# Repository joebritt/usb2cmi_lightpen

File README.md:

# usb2cmi_lightpen
Use a USB mouse instead of (or in conjunction with) the lightpen on a Fairlight CMI.

# Basic Idea

The interface generates lightpen emulation signals that make the CMI video hardware "think" a lightpen is there. The signals are generated to create a small (smaller than is normal with the real lightpen) cursor on the screen.

Moving the mouse, you will see the on-screen cursor track the mouse movement.

Clicking the left button (or button, if it's a 1-button mouse) is like touching the tip of the real lightpen.

If the mouse has a right button, clicking it will toggle the cursor off and on.

If a real lightpen is fitted to the VDU, it will continue to work in conjunction with the mouse.
Normally, the mouse cursor will be shown on the screen. If you bring the lightpen to the screen,
the lightpen cursor will appear and the mouse cursor will disappear. You can then interact using
the lightpen as normal. When you move the lightpen away from the screen, the mouse cursor will
reappear.

# Version 1
[Version 1 PCB](https://oshpark.com/shared_projects/1uISLCAx)</br>

V1 is the original external box style interface. It is powered by a 5V AC adapter.

Both versions have 2 LEDs. These are used to show the status of the video signal (flashes if no video
detected) and presence of a mouse (off if no mouse detected).

V1 has an RCA jack which provides unbuffered access to the CMI video signal. Since it is
unbuffered, the legacy VDU cannot (normally) be used at the same time as the RCA jack.
(V2 buffers the video signal to allow this use case.)

# Version 2
[Version 2 PCB](https://oshpark.com/shared_projects/5qV4mRA7)</br>

V2 is an updated version that fits completely inside the CMI. It is the same core hardware design.

Differences:
  - No AC power supply needed, it is powered from 5V that is tapped from the CMI front panel board
  - RCA jack provides a buffered CMI video signal, so it and the VDU may be used simultaneously
  - Video RCA jack and USB connector are routed to a panel that mounts to the CMI bottom pan
  - laser-cut "wings" attach to the interface board and let it occupy an unused CMI slot

The CMI Series I and II have a slightly different connection to the front panel board. On those
machines, an adapter board is used to convert to a IIX-style connector that the interface board
can connect to.

## Firmware

Some work will be needed to get the code to build with the latest Microchip MPLAB X tools,
so I recommend installing the v8.63 release of MPLAB (pre-MPLAB X). 

Microchip is good about making legacy tools available, you can find version 8.63 here:

https://www.microchip.com/development-tools/pic-and-dspic-downloads-archive

*You don't have to build the code from source:*

In the "prebuilt_hexfiles" folder are pre-compiled images of the bootloader and lightpen emulation application.

To use these:

- Use the Microchip tools to flash bootloader.hex into the PIC32.
- Put cmimouse.hex on a USB thumbdrive (formatted with a DOS/FAT filesystem).
- Plug the thumbdrive into the interface USB port and power up the board.
- You should see the leds blink back and forth, then the cmimouse.hex file will be copied from the thumbdrive to the PIC32 flash.
- You'll see the LEDs change their flashing pattern when the code is flashed and started.
- Unplug the thumbdrive, plug in a mouse, and you should see the mouse status LED turn ON.
- If you connect the unit to the CMI and power on the CMI, you should see the video status LED stop flashing and go solid ON, and the cursor appear on the CMI video output.

## Hardware

The PCB design tool Eagle was used for all PCBs. 
The Eagle .brd files can be easily uploaded to OSHPark (https://oshpark.com/) for fabrication. Of course, you can use any board house you like to make them.
All boards are 2 layer, 6mil minimum trace/space, and 10mil minimum drill.

The aluminum front panel (for Version 1) and the aluminum rear panel (for Version 2) were designed using Front Panel Designer and fabricated using Front Panel Express (https://www.frontpanelexpress.com/).
Eagle was used as a crude 2D mechanical CAD for the Version 2 rear panel and the Version 2 mounting wings. 
Board files and generated PDFs and XPS files for these are included. The XPS files were used to drive a laser cutter to make prototypes of the rear panel and to make the actual mounting wings.

## Cabling

### Version 1

The 5-pin XLR cable from the CMI to the monitor ("VDU" in Fairlight parlance) connects
to the box. This cable carries a monochrome composite video signal with PAL timing from the CMI
and 2 TTL level signals from the lightpen to the CMI. 

These 3 signals are carried over 3x 75 ohm coax cables bundled together and sheathed similar to
an analog RGB video cable. The pinout for this cable is not straight-through, please see the
details in the monitor_cable folder.

Using two of these 5-pin XLR cables, the box is connected between the CMI and VDU.
Of course, the box can be used without the VDU, in which case only one 5-pin XLR cable is needed.

### Version 2

Version 2 doesn't need the external 5-pin XLR cabling, but does need several smaller internal cables:

- 1x 26-way ribbon cable with a female IDC connector at each end, taps power from CMI front panel
- 1x (CMI IIX) or 2x (CMI I or II) 10-way ribbon cable with a female IDC connector at each end for video & LP signals
- 1x USB Type A to Type B bulkead connector extension, routes USB connection on board to rear panel
- 1x RCA male/male extension, routes video from RCA jack on board to rear panel RCA jack
- 1x RCA female/female bulkhead connector, pass video from internal extension cable to external jack

## Mounting Hardware

### Version 1

The plastic box that was used for Version 1 is off-the-shelf from Radio Shack. It appears that they
still carry this box: https://www.radioshack.com/products/radioshack-project-enclosure-6x3x2?variant=20332261445

The aluminum front panel is designed to replace the blank aluminum panel that comes with the box.

The PCB attaches to the aluminum front panel with the 4 XLR connector screws and floats inside the box.

### Version 2

The 2 laser-cut plastic wings attach to the PCB with 4x M3 screws, nuts, and lockwashers. There are 2 versions
of the wings -- I thought the originals were a little too long, so I made a version 1cm shorter. Both work fine, but the longer ones may cause the internal USB connector to rub against the inside of the front panel door.

For the rear panel, countersunk holes are provided in the aluminum panel to accept the screws originally used to hold the Fairlight factory-provided blank cover panel. Remove the blank panel, use the screws and nuts to affix the new aluminum video/USB jack panel.

The bulkhead female/female RCA connector has 1 large nut which should be on the inside face of the panel.
The bulkhead USB connector has 2 M3 screws that hold it in place.

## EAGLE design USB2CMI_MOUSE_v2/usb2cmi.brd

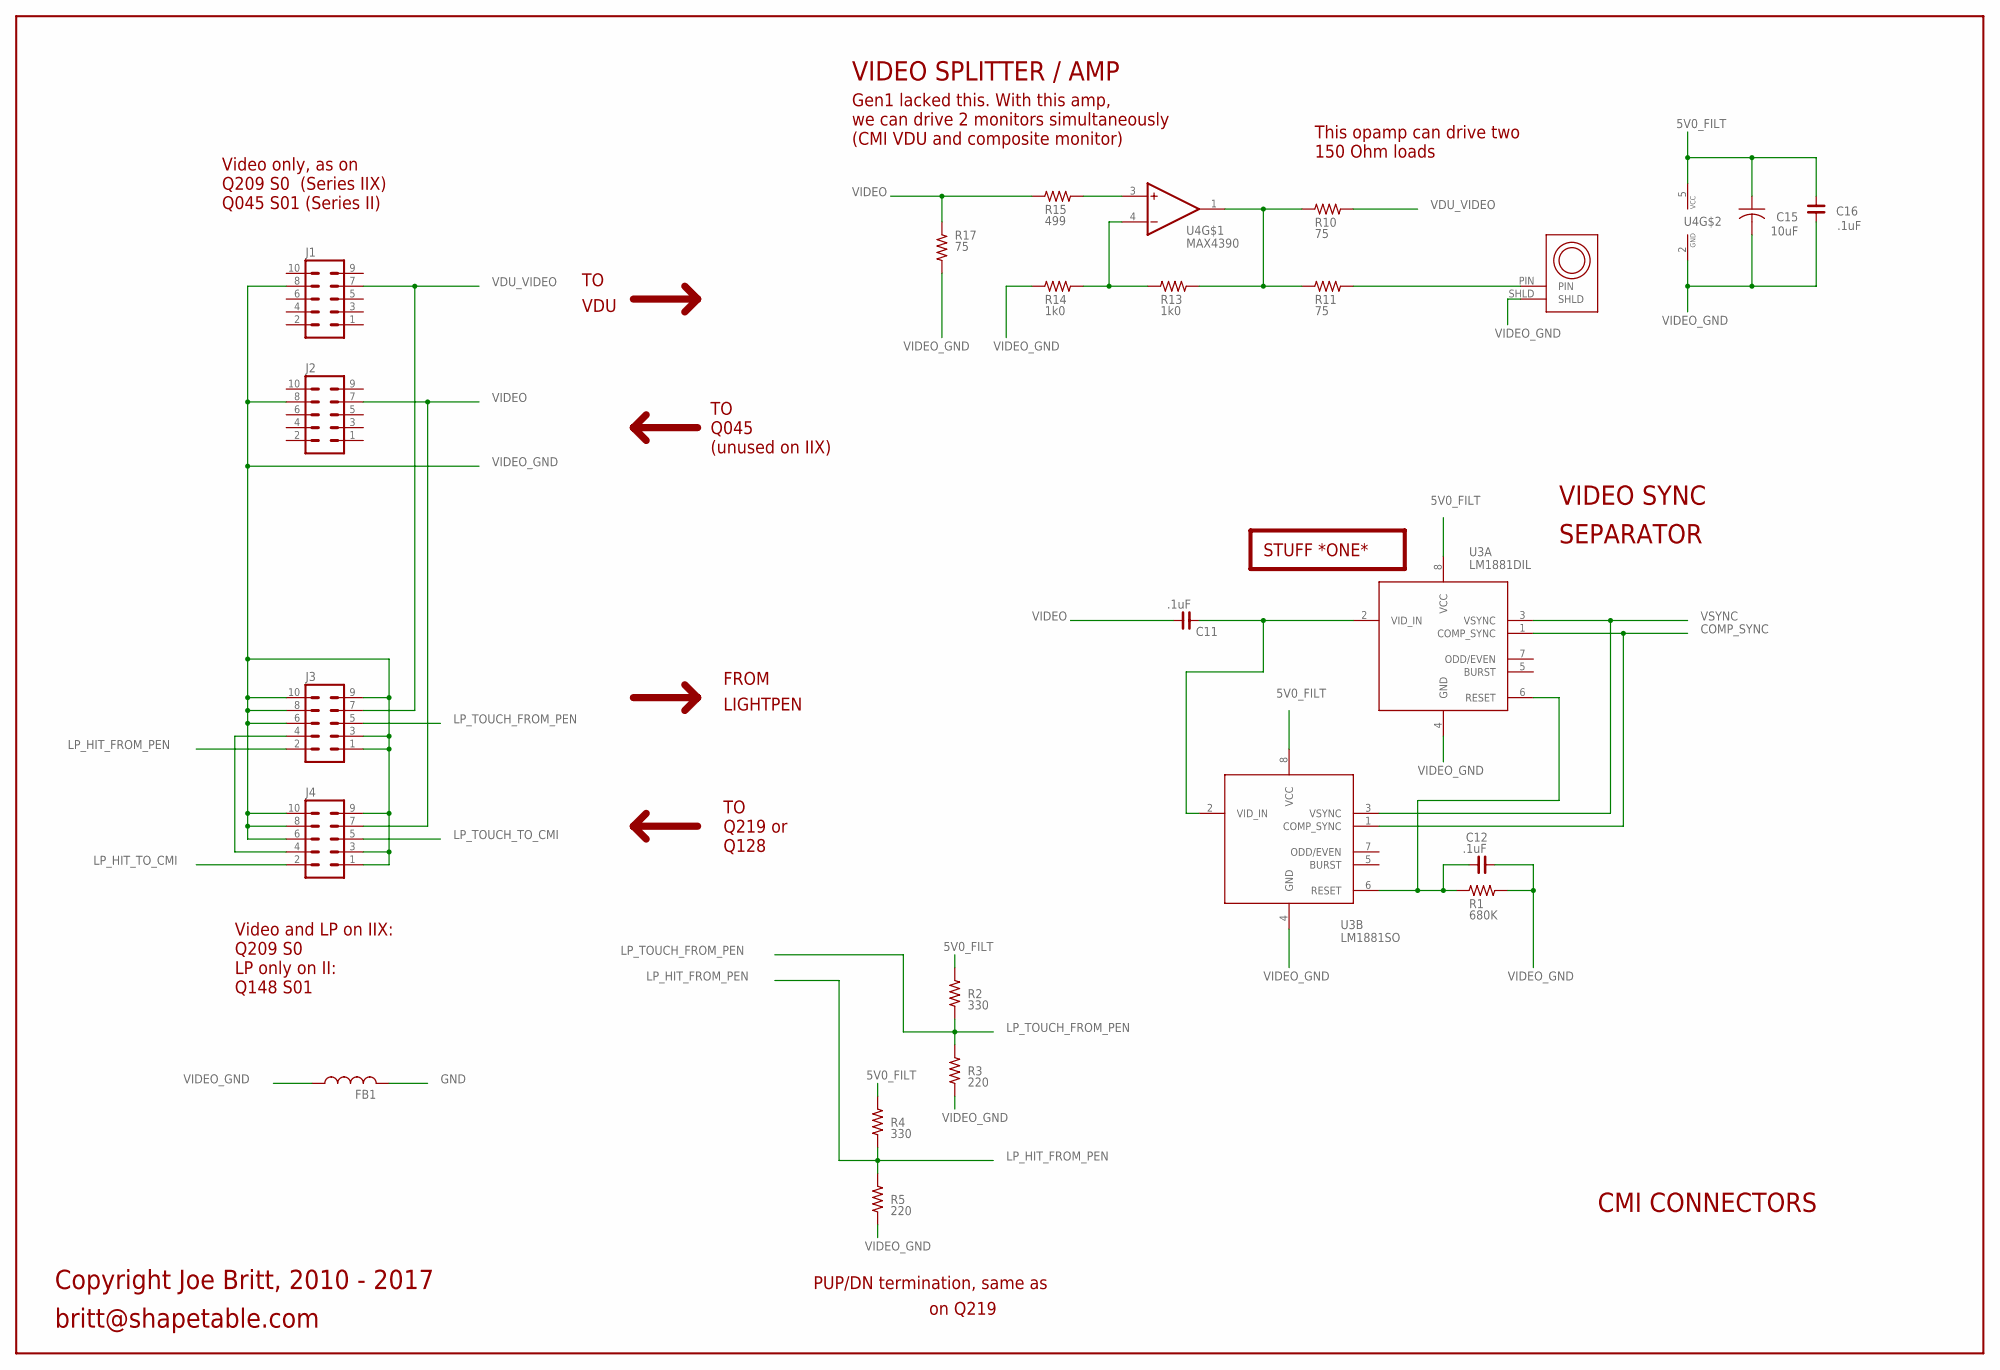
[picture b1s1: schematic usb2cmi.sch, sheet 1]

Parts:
C11, C12, C16: .1uF; C0603
C15: 10uF; C0805
FB1: L-US0207/15; 0207/15
J1, J3: 10H
J2, J4: ML10
J8: CUI RCJ-044; RCA-SHIELDED
R1: 680K; R0603
R2, R4: 330; R0603
R3, R5: 220; R0603
R10, R11, R17: 75; R0603
R13, R14: 1k0; R0603
R15: 499; R0603
U3A: LM1881DIL; DIL08
U3B: LM1881SO; SO08
U4: MAX4390; SOT23-5L

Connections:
5V0_FILT: C15.1, C16.2, R2.2, R4.2, U3A.8 (VCC), U3B.8 (VCC), U4.5 (VCC); also elsewhere on the board
COMP_SYNC: U3A.1 (COMP_SYNC), U3B.1 (COMP_SYNC); also elsewhere on the board
GND: FB1.2; also elsewhere on the board
LP_HIT_FROM_PEN: J3.2, R4.1, R5.2; also elsewhere on the board
LP_HIT_TO_CMI: J4.2; also elsewhere on the board
LP_TOUCH_FROM_PEN: J3.5, R2.1, R3.2; also elsewhere on the board
LP_TOUCH_TO_CMI: J4.5; also elsewhere on the board
unnamed: J3.4, J4.4
unnamed: C11.2, U3A.2 (VID_IN), U3B.2 (VID_IN)
unnamed: C12.1, R1.2, U3A.6 (RESET), U3B.6 (RESET)
unnamed: R10.2, R11.2, R13.1, U4.1 (OUT)
unnamed: J8.PIN, R11.1
unnamed: R13.2, R14.1, U4.4 (-IN)
unnamed: R15.1, U4.3 (+IN)
VDU_VIDEO: J1.7, J3.7, R10.1
VIDEO: C11.1, J2.7, J4.7, R15.2, R17.1
VIDEO_GND: C12.2, C15.2, C16.1, FB1.1, J1.8, J2.8, J3.1, J3.3, J3.6, J3.8, J3.9, J3.10, J4.1, J4.3, J4.6, J4.8, J4.9, J4.10, J8.SHLD, R1.1, R3.1, R5.1, R14.2, R17.2, U3A.4 (GND), U3B.4 (GND), U4.2 (GND); also elsewhere on the board
VSYNC: U3A.3 (VSYNC), U3B.3 (VSYNC); also elsewhere on the board

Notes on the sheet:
VDU
Q045 (unused on IIX)
STUFF *ONE*
VIDEO SYNC
SEPARATOR
CMI CONNECTORS
PUP/DN termination, same as
on Q219
Copyright Joe Britt, 2010 - 2017
britt@shapetable.com
Video only, as on Q209 S0 (Series IIX) Q045 S01 (Series II)
Video and LP on IIX: Q209 S0 LP only on II: Q148 S01
FROM
LIGHTPEN
Q219 or Q128
VIDEO SPLITTER / AMP
Gen1 lacked this. With this amp, we can drive 2 monitors simultaneously (CMI VDU and composite monitor)
This opamp can drive two 150 Ohm loads

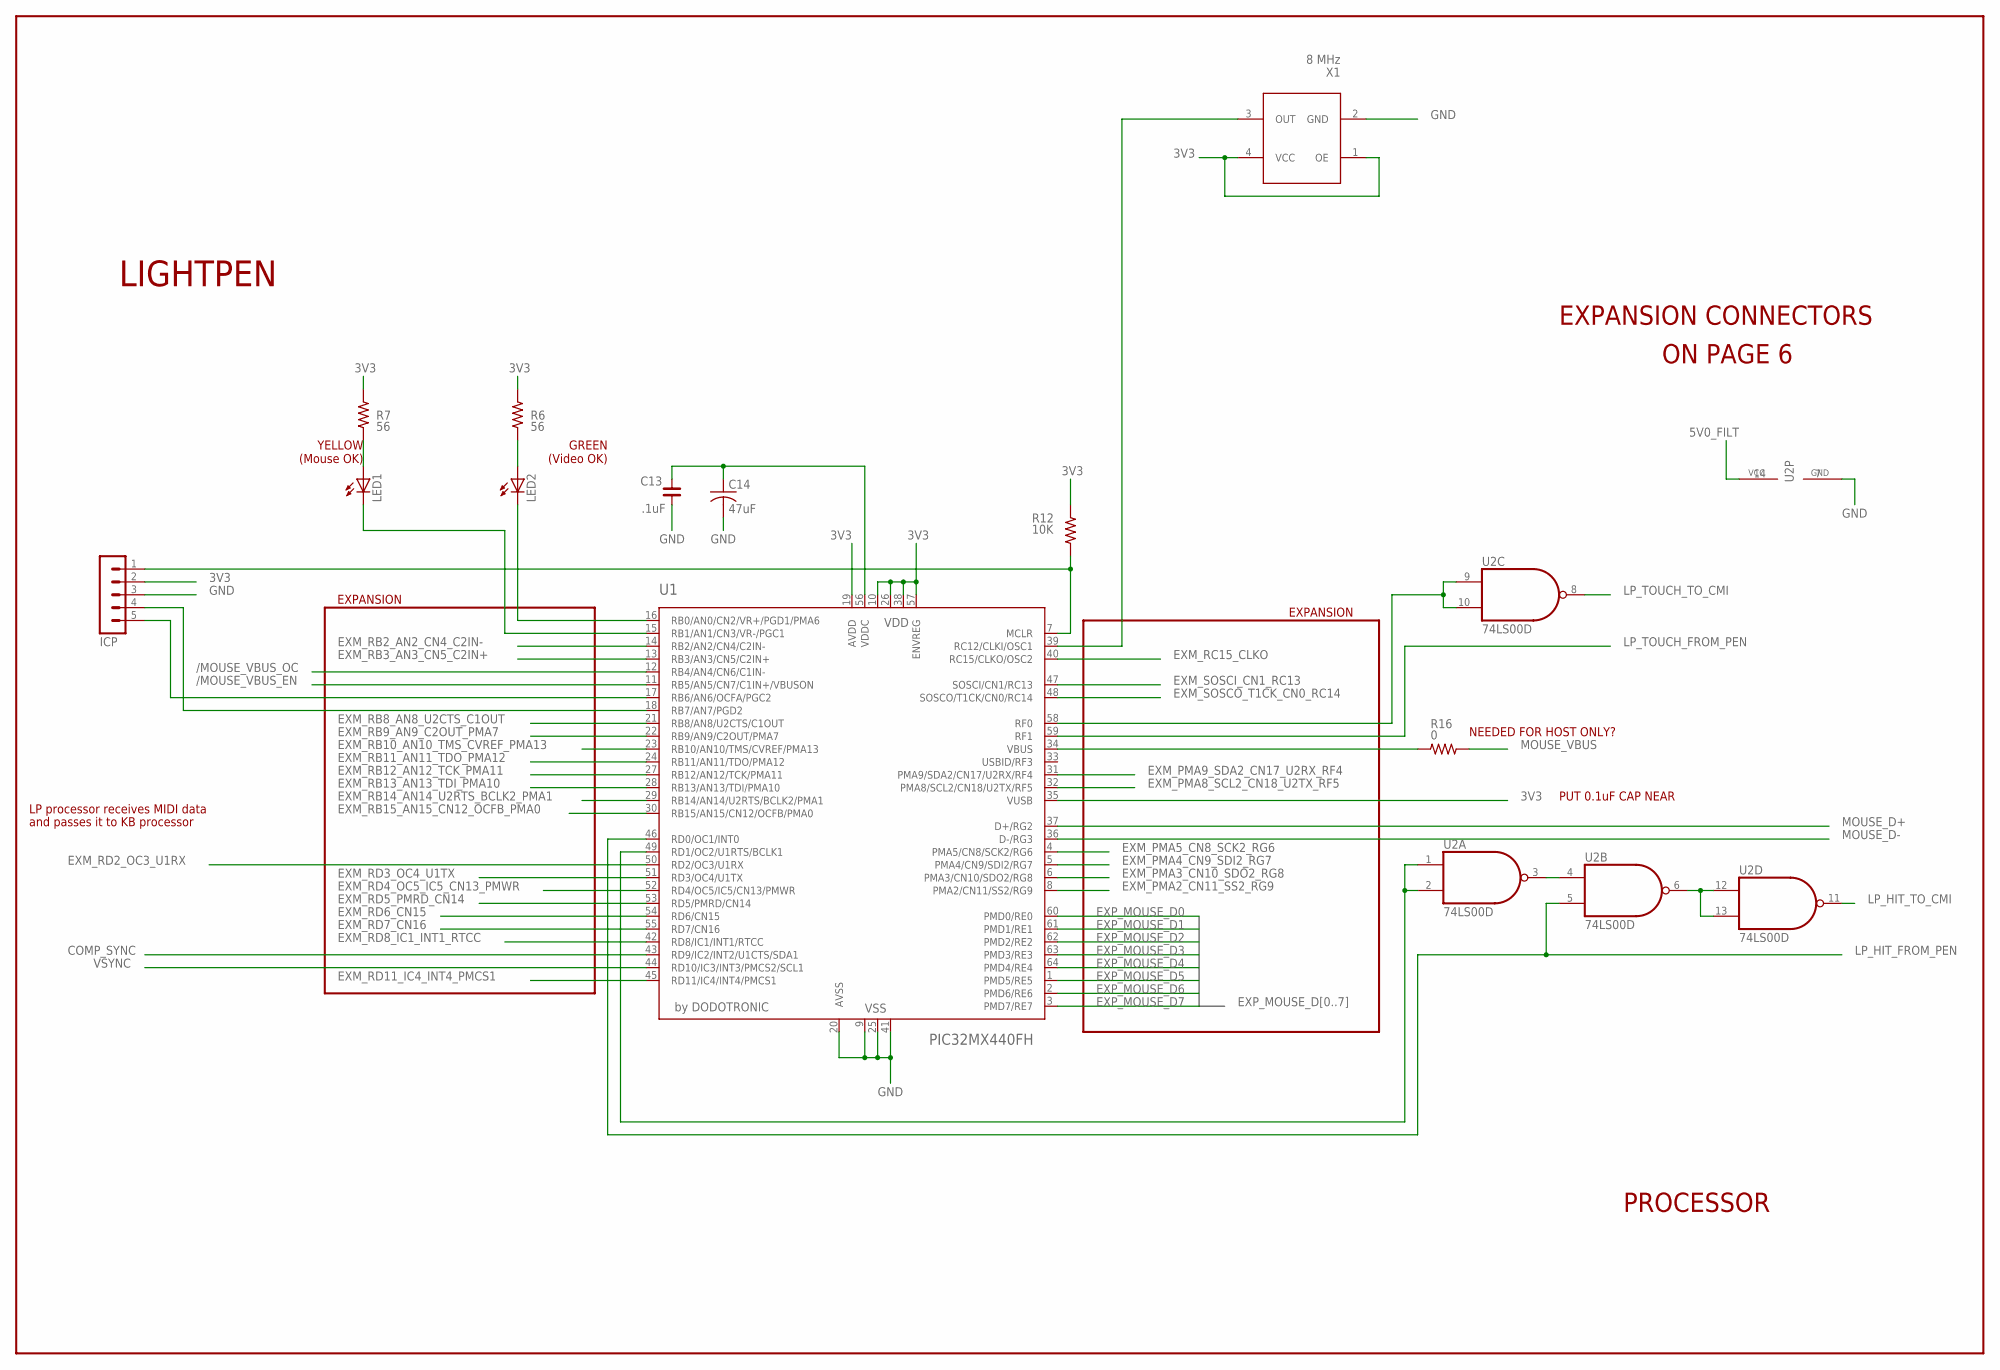
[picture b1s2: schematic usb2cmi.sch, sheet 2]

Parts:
C13: .1uF; C0603
C14: 47uF; C0805
ICP: MA05-1
LED1, LED2: LEDCHIPLED_0805; CHIPLED_0805
R6, R7: 56; R0603
R12: 10K; R0603
R16: 0; R0603
U1: PIC32MX440FH; TQFP64-10X10
U2: 74LS00D; SO14
X1: 8 MHz; CTS-OSC

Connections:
3V3: ICP.2, R6.2, R7.2, R12.2, U1.10 (VDD), U1.19 (AVDD), U1.26 (VDD), U1.35 (VUSB), U1.38 (VDD), U1.57 (ENVREG), X1.1 (OE), X1.4 (VCC); also elsewhere on the board
5V0_FILT: U2.14 (VCC); also elsewhere on the board
/MOUSE_VBUS_EN: U1.11 (RB5/AN5/CN7/C1IN+/VBUSON); also elsewhere on the board
/MOUSE_VBUS_OC: U1.12 (RB4/AN4/CN6/C1IN-); also elsewhere on the board
COMP_SYNC: U1.43 (RD9/IC2/INT2/U1CTS/SDA1); also elsewhere on the board
EXM_PMA2_CN11_SS2_RG9: U1.8 (PMA2/CN11/SS2/RG9)
EXM_PMA3_CN10_SDO2_RG8: U1.6 (PMA3/CN10/SDO2/RG8)
EXM_PMA4_CN9_SDI2_RG7: U1.5 (PMA4/CN9/SDI2/RG7)
EXM_PMA5_CN8_SCK2_RG6: U1.4 (PMA5/CN8/SCK2/RG6)
EXM_PMA8_SCL2_CN18_U2TX_RF5: U1.32 (PMA8/SCL2/CN18/U2TX/RF5); also elsewhere on the board
EXM_PMA9_SDA2_CN17_U2RX_RF4: U1.31 (PMA9/SDA2/CN17/U2RX/RF4); also elsewhere on the board
EXM_RB0_AN0_CN2_PMA6: LED2.C, U1.16 (RB0/AN0/CN2/VR+/PGD1/PMA6)
EXM_RB2_AN2_CN4_C2IN-: U1.14 (RB2/AN2/CN4/C2IN-)
EXM_RB3_AN3_CN5_C2IN+: U1.13 (RB3/AN3/CN5/C2IN+)
EXM_RB8_AN8_U2CTS_C1OUT: U1.21 (RB8/AN8/U2CTS/C1OUT)
EXM_RB9_AN9_C2OUT_PMA7: U1.22 (RB9/AN9/C2OUT/PMA7)
EXM_RB10_AN10_TMS_CVREF_PMA13: U1.23 (RB10/AN10/TMS/CVREF/PMA13)
EXM_RB11_AN11_TDO_PMA12: U1.24 (RB11/AN11/TDO/PMA12)
EXM_RB12_AN12_TCK_PMA11: U1.27 (RB12/AN12/TCK/PMA11)
EXM_RB13_AN13_TDI_PMA10: U1.28 (RB13/AN13/TDI/PMA10)
EXM_RB14_AN14_U2RTS_BCLK2_PMA1: U1.29 (RB14/AN14/U2RTS/BCLK2/PMA1)
EXM_RB15_AN15_CN12_OCFB_PMA0: U1.30 (RB15/AN15/CN12/OCFB/PMA0)
EXM_RC15_CLKO: U1.40 (RC15/CLKO/OSC2)
EXM_RD2_OC3_U1RX: U1.50 (RD2/OC3/U1RX); also elsewhere on the board
EXM_RD3_OC4_U1TX: U1.51 (RD3/OC4/U1TX); also elsewhere on the board
EXM_RD4_OC5_IC5_CN13_PMWR: U1.52 (RD4/OC5/IC5/CN13/PMWR)
EXM_RD5_PMRD_CN14: U1.53 (RD5/PMRD/CN14)
EXM_RD6_CN15: U1.54 (RD6/CN15)
EXM_RD7_CN16: U1.55 (RD7/CN16)
EXM_RD8_IC1_INT1_RTCC: U1.42 (RD8/IC1/INT1/RTCC)
EXM_RD11_IC4_INT4_PMCS1: U1.45 (RD11/IC4/INT4/PMCS1)
EXM_SOSCI_CN1_RC13: U1.47 (SOSCI/CN1/RC13)
EXM_SOSCO_T1CK_CN0_RC14: U1.48 (SOSCO/T1CK/CN0/RC14)
EXP_MOUSE_D0: U1.60 (PMD0/RE0)
EXP_MOUSE_D1: U1.61 (PMD1/RE1)
EXP_MOUSE_D2: U1.62 (PMD2/RE2)
EXP_MOUSE_D3: U1.63 (PMD3/RE3)
EXP_MOUSE_D4: U1.64 (PMD4/RE4)
EXP_MOUSE_D5: U1.1 (PMD5/RE5)
EXP_MOUSE_D6: U1.2 (PMD6/RE6)
EXP_MOUSE_D7: U1.3 (PMD7/RE7)
GND: C13.2, C14.2, ICP.3, U1.9 (VSS), U1.20 (AVSS), U1.25 (VSS), U1.41 (VSS), U2.7 (GND), X1.2 (GND); also elsewhere on the board
LP_HIT_FROM_PEN: U1.46 (RD0/OC1/INT0), U2.5 (I1); also elsewhere on the board
LP_HIT_TO_CMI: U2.11 (O); also elsewhere on the board
LP_TOUCH_FROM_PEN: U1.59 (RF1); also elsewhere on the board
LP_TOUCH_TO_CMI: U2.8 (O); also elsewhere on the board
MOUSE_D+: U1.37 (D+/RG2); also elsewhere on the board
MOUSE_D-: U1.36 (D-/RG3); also elsewhere on the board
MOUSE_VBUS: R16.1; also elsewhere on the board
unnamed: C13.1, C14.1, U1.56 (VDDC)
unnamed: LED2.A, R6.1
unnamed: LED1.C, U1.15 (RB1/AN1/CN3/VR-/PGC1)
unnamed: U1.39 (RC12/CLKI/OSC1), X1.3 (OUT)
unnamed: U1.58 (RF0), U2.9 (I0), U2.10 (I1)
unnamed: U2.6 (O), U2.12 (I0), U2.13 (I1)
unnamed: U2.3 (O), U2.4 (I0)
unnamed: U1.49 (RD1/OC2/U1RTS/BCLK1), U2.1 (I0), U2.2 (I1)
unnamed: LED1.A, R7.1
unnamed: R16.2, U1.34 (VBUS)
PGC: ICP.5, U1.17 (RB6/AN6/OCFA/PGC2)
PGD: ICP.4, U1.18 (RB7/AN7/PGD2)
U2_MCLR: ICP.1, R12.1, U1.7 (MCLR)
VSYNC: U1.44 (RD10/IC3/INT3/PMCS2/SCL1); also elsewhere on the board

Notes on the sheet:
LIGHTPEN
YELLOW (Mouse OK)
NEEDED FOR HOST ONLY?
PUT 0.1uF CAP NEAR
EXPANSION CONNECTORS
ON PAGE 6
PROCESSOR
EXPANSION
LP processor receives MIDI data
and passes it to KB processor
GREEN (Video OK)

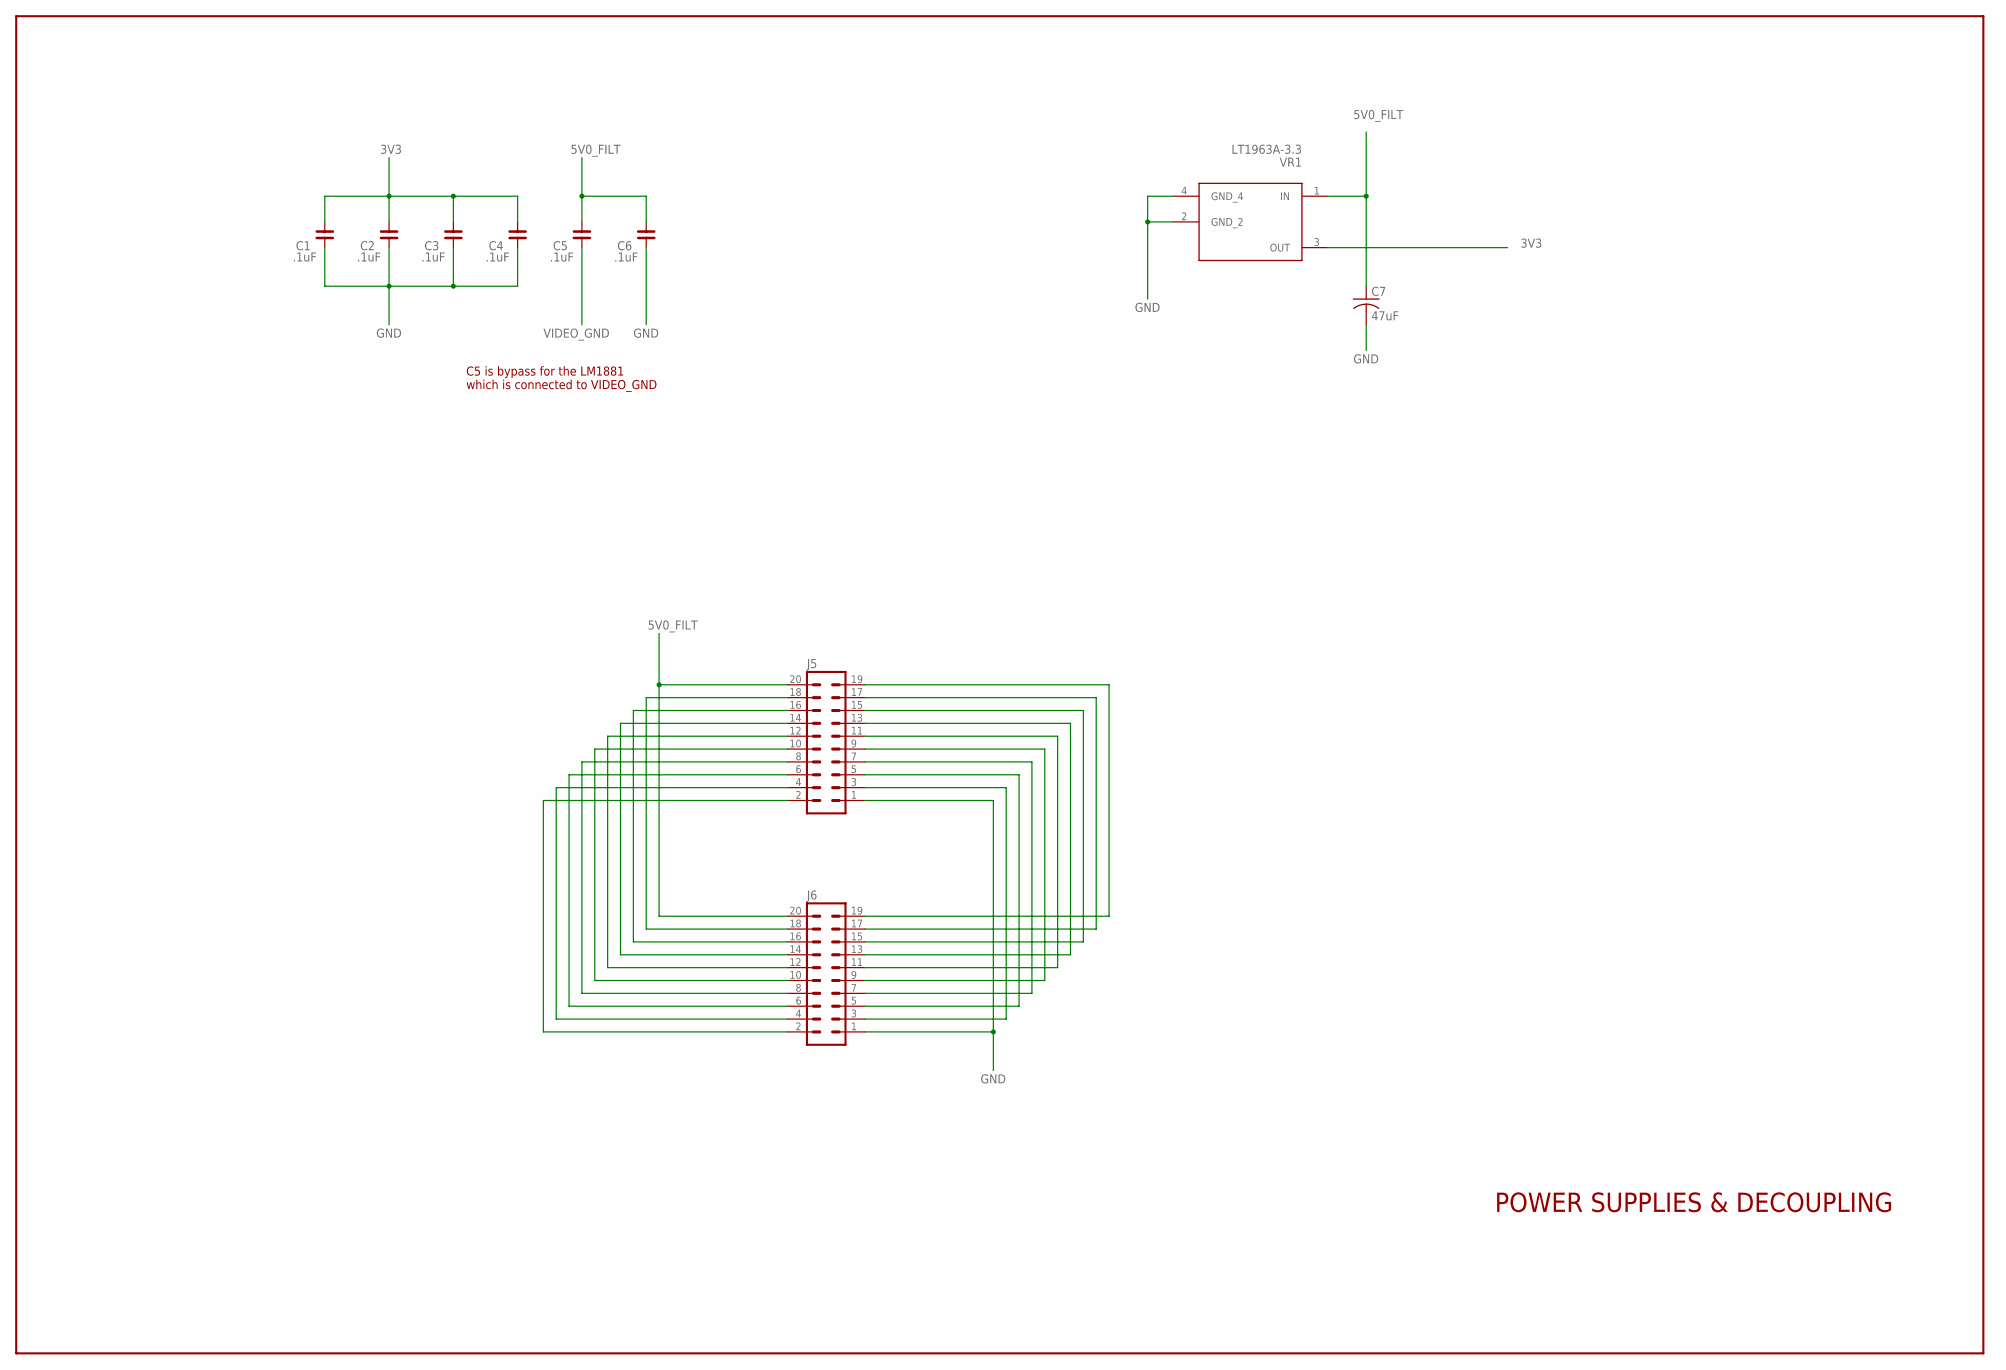
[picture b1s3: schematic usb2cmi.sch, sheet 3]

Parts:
C1, C2, C3, C4, C5, C6: .1uF; C0603
C7: 47uF; C0805
J5: 20H
J6: ML20
VR1: LT1963A-3.3; SOT-223

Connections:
3V3: C1.1, C2.1, C3.1, C4.1, VR1.3 (OUT); also elsewhere on the board
5V0_FILT: C5.1, C6.1, C7.1, J5.20, J6.20, VR1.1 (IN); also elsewhere on the board
GND: C1.2, C2.2, C3.2, C4.2, C6.2, C7.2, J5.1, J6.1, VR1.2 (GND_2), VR1.4 (GND_4); also elsewhere on the board
unnamed: J5.18, J6.18
unnamed: J5.16, J6.16
unnamed: J5.14, J6.14
unnamed: J5.12, J6.12
unnamed: J5.10, J6.10
unnamed: J5.8, J6.8
unnamed: J5.6, J6.6
unnamed: J5.4, J6.4
unnamed: J5.2, J6.2
unnamed: J5.3, J6.3
unnamed: J5.5, J6.5
unnamed: J5.7, J6.7
unnamed: J5.9, J6.9
unnamed: J5.11, J6.11
unnamed: J5.13, J6.13
unnamed: J5.15, J6.15
unnamed: J5.17, J6.17
unnamed: J5.19, J6.19
VIDEO_GND: C5.2; also elsewhere on the board

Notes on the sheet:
POWER SUPPLIES & DECOUPLING
C5 is bypass for the LM1881 which is connected to VIDEO_GND

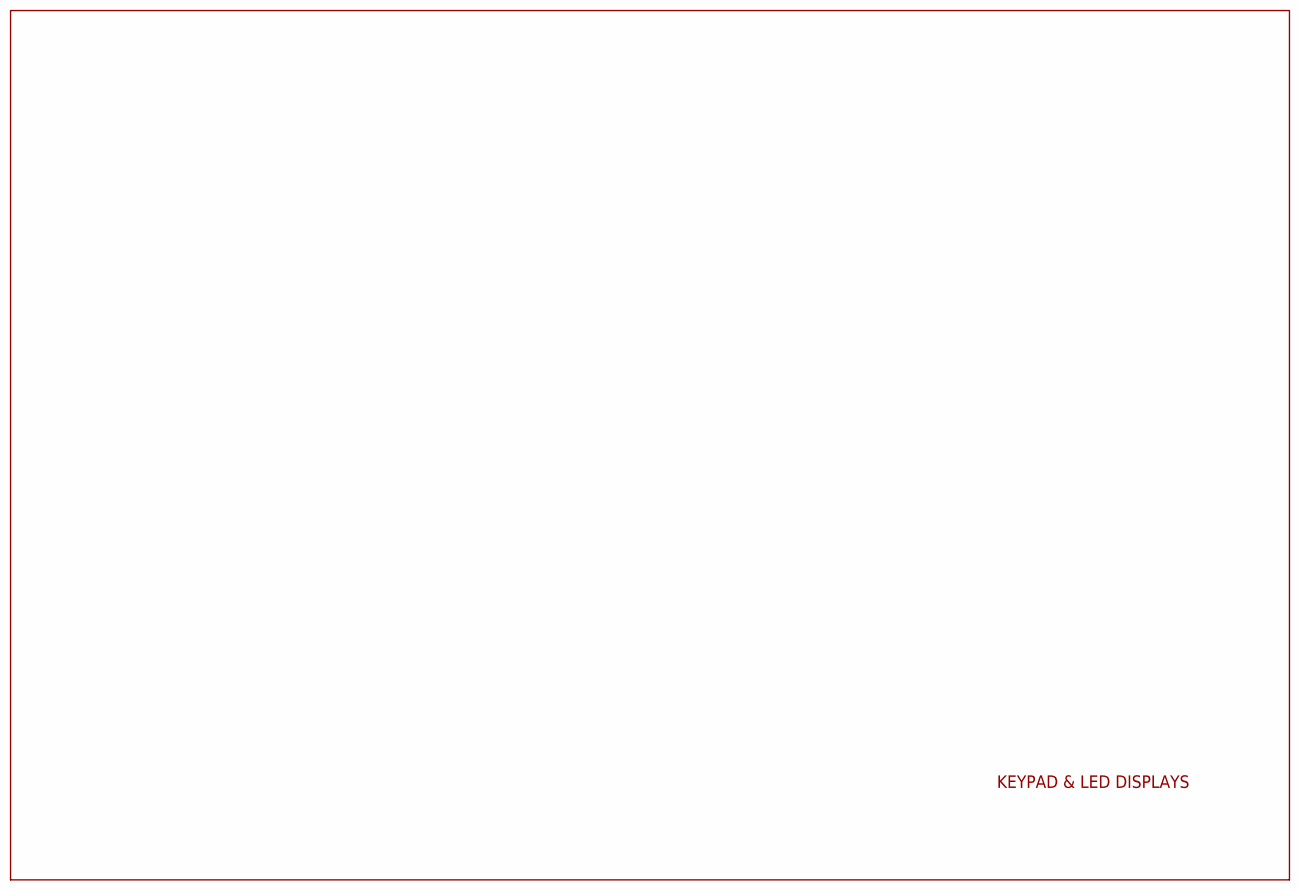
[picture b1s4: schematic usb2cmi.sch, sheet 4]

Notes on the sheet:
KEYPAD & LED DISPLAYS

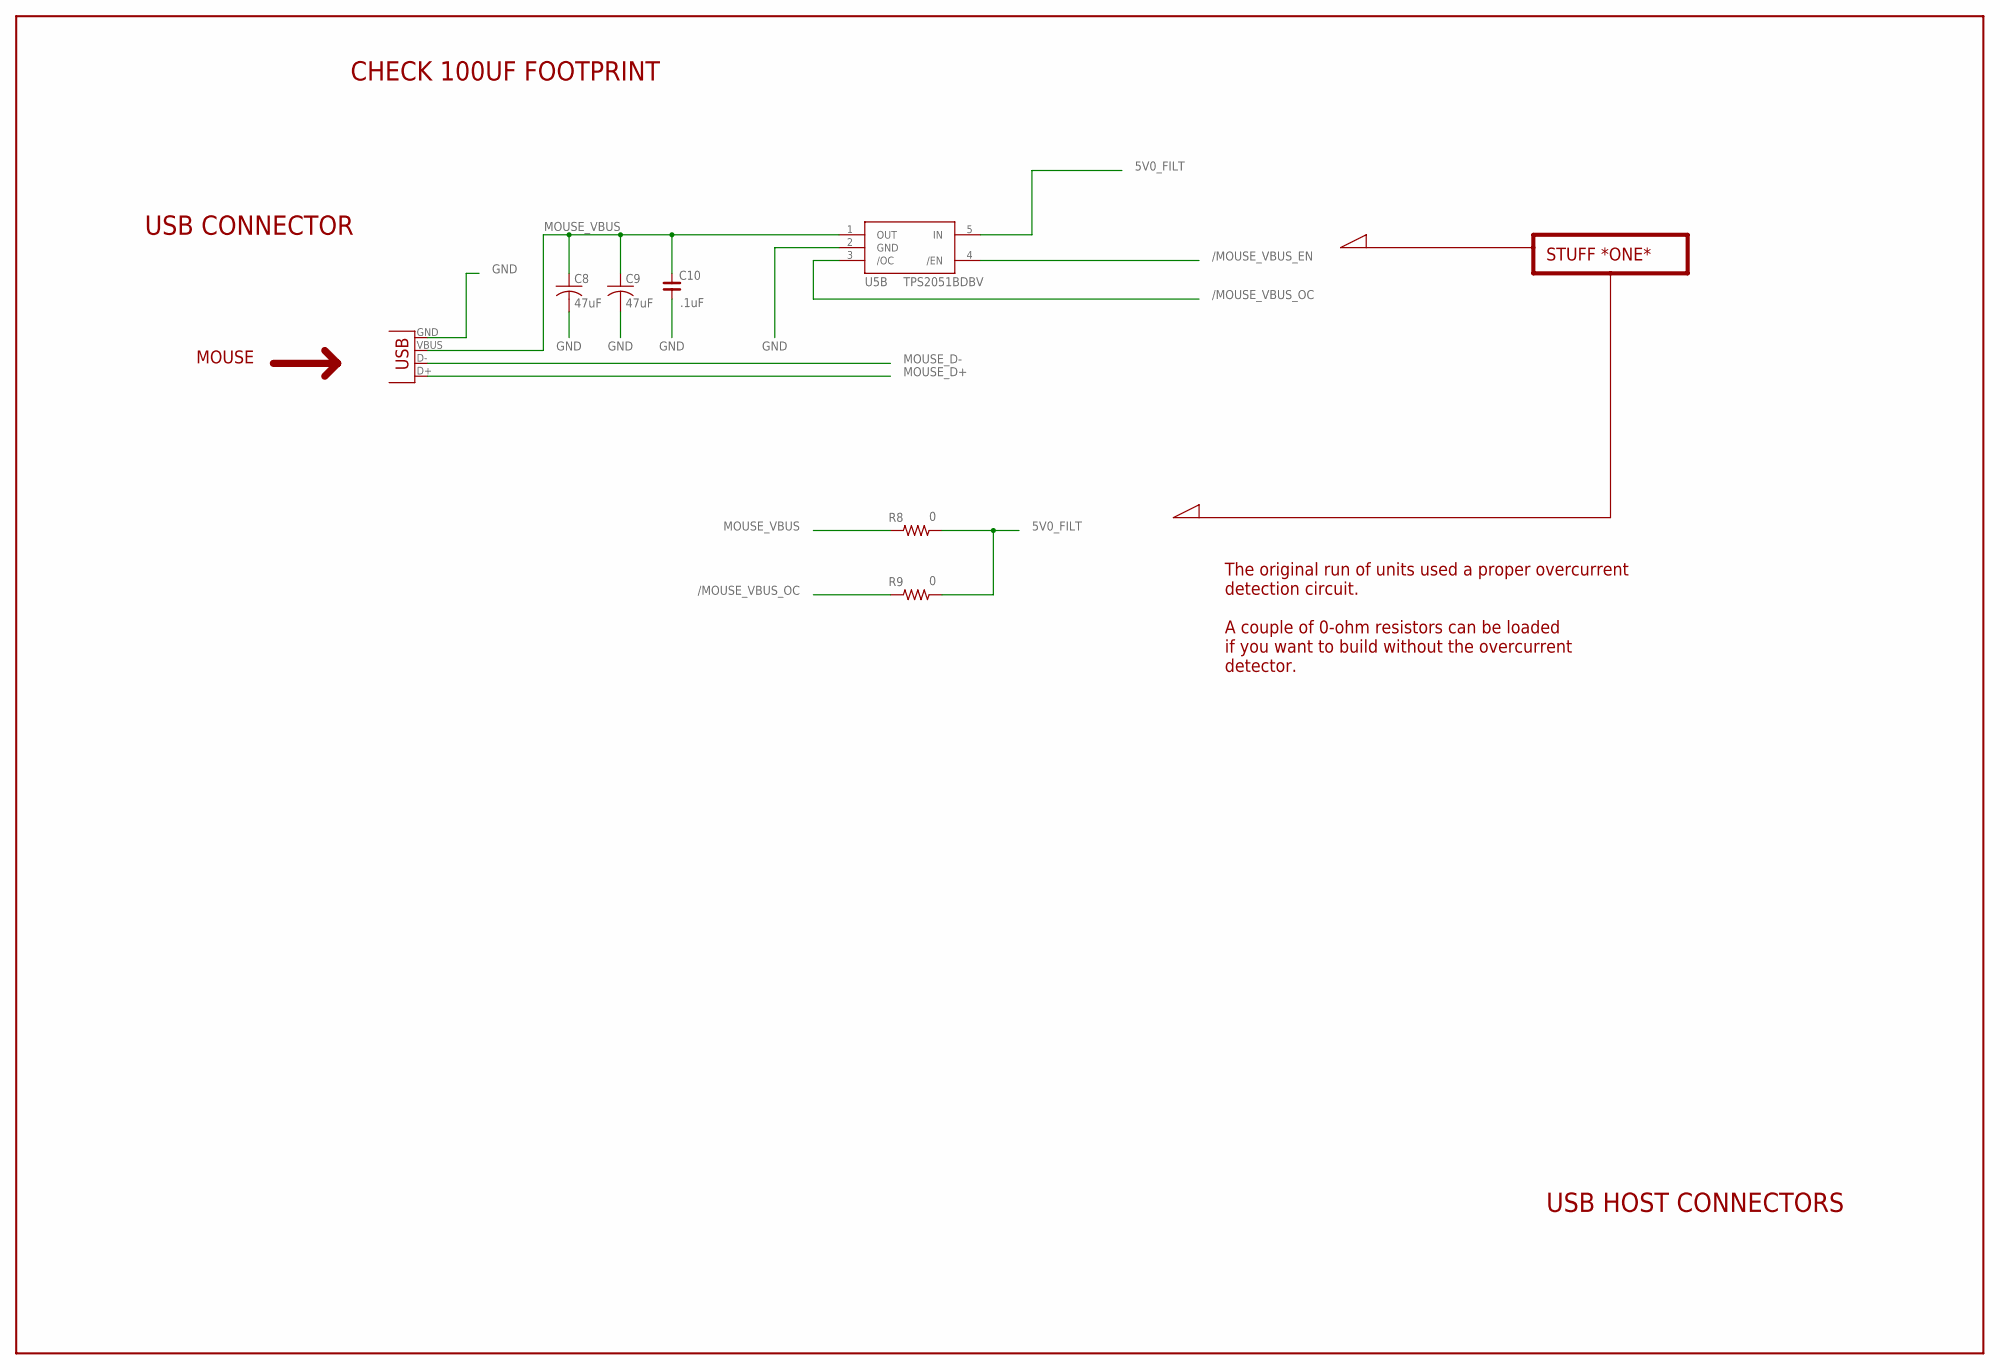
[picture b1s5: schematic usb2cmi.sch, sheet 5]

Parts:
C8, C9: 47uF; C0805
C10: .1uF; C0603
J7: USB-A-H
R8, R9: 0; R0603
U5B: TPS2051BDBV; DBV-5

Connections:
5V0_FILT: R8.1, R9.1, U5B.5 (IN); also elsewhere on the board
/MOUSE_VBUS_EN: U5B.4 (/EN); also elsewhere on the board
/MOUSE_VBUS_OC: R9.2, U5B.3 (/OC); also elsewhere on the board
GND: C8.2, C9.2, C10.2, J7.GND, U5B.2 (GND); also elsewhere on the board
MOUSE_D+: J7.D+; also elsewhere on the board
MOUSE_D-: J7.D-; also elsewhere on the board
MOUSE_VBUS: C8.1, C9.1, C10.1, J7.VBUS, R8.2, U5B.1 (OUT); also elsewhere on the board

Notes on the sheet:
MOUSE
USB CONNECTOR
STUFF *ONE*
CHECK 100UF FOOTPRINT
USB HOST CONNECTORS
The original run of units used a proper overcurrent detection circuit. A couple of 0-ohm resistors can be loaded if you want to build without the overcurrent detector.

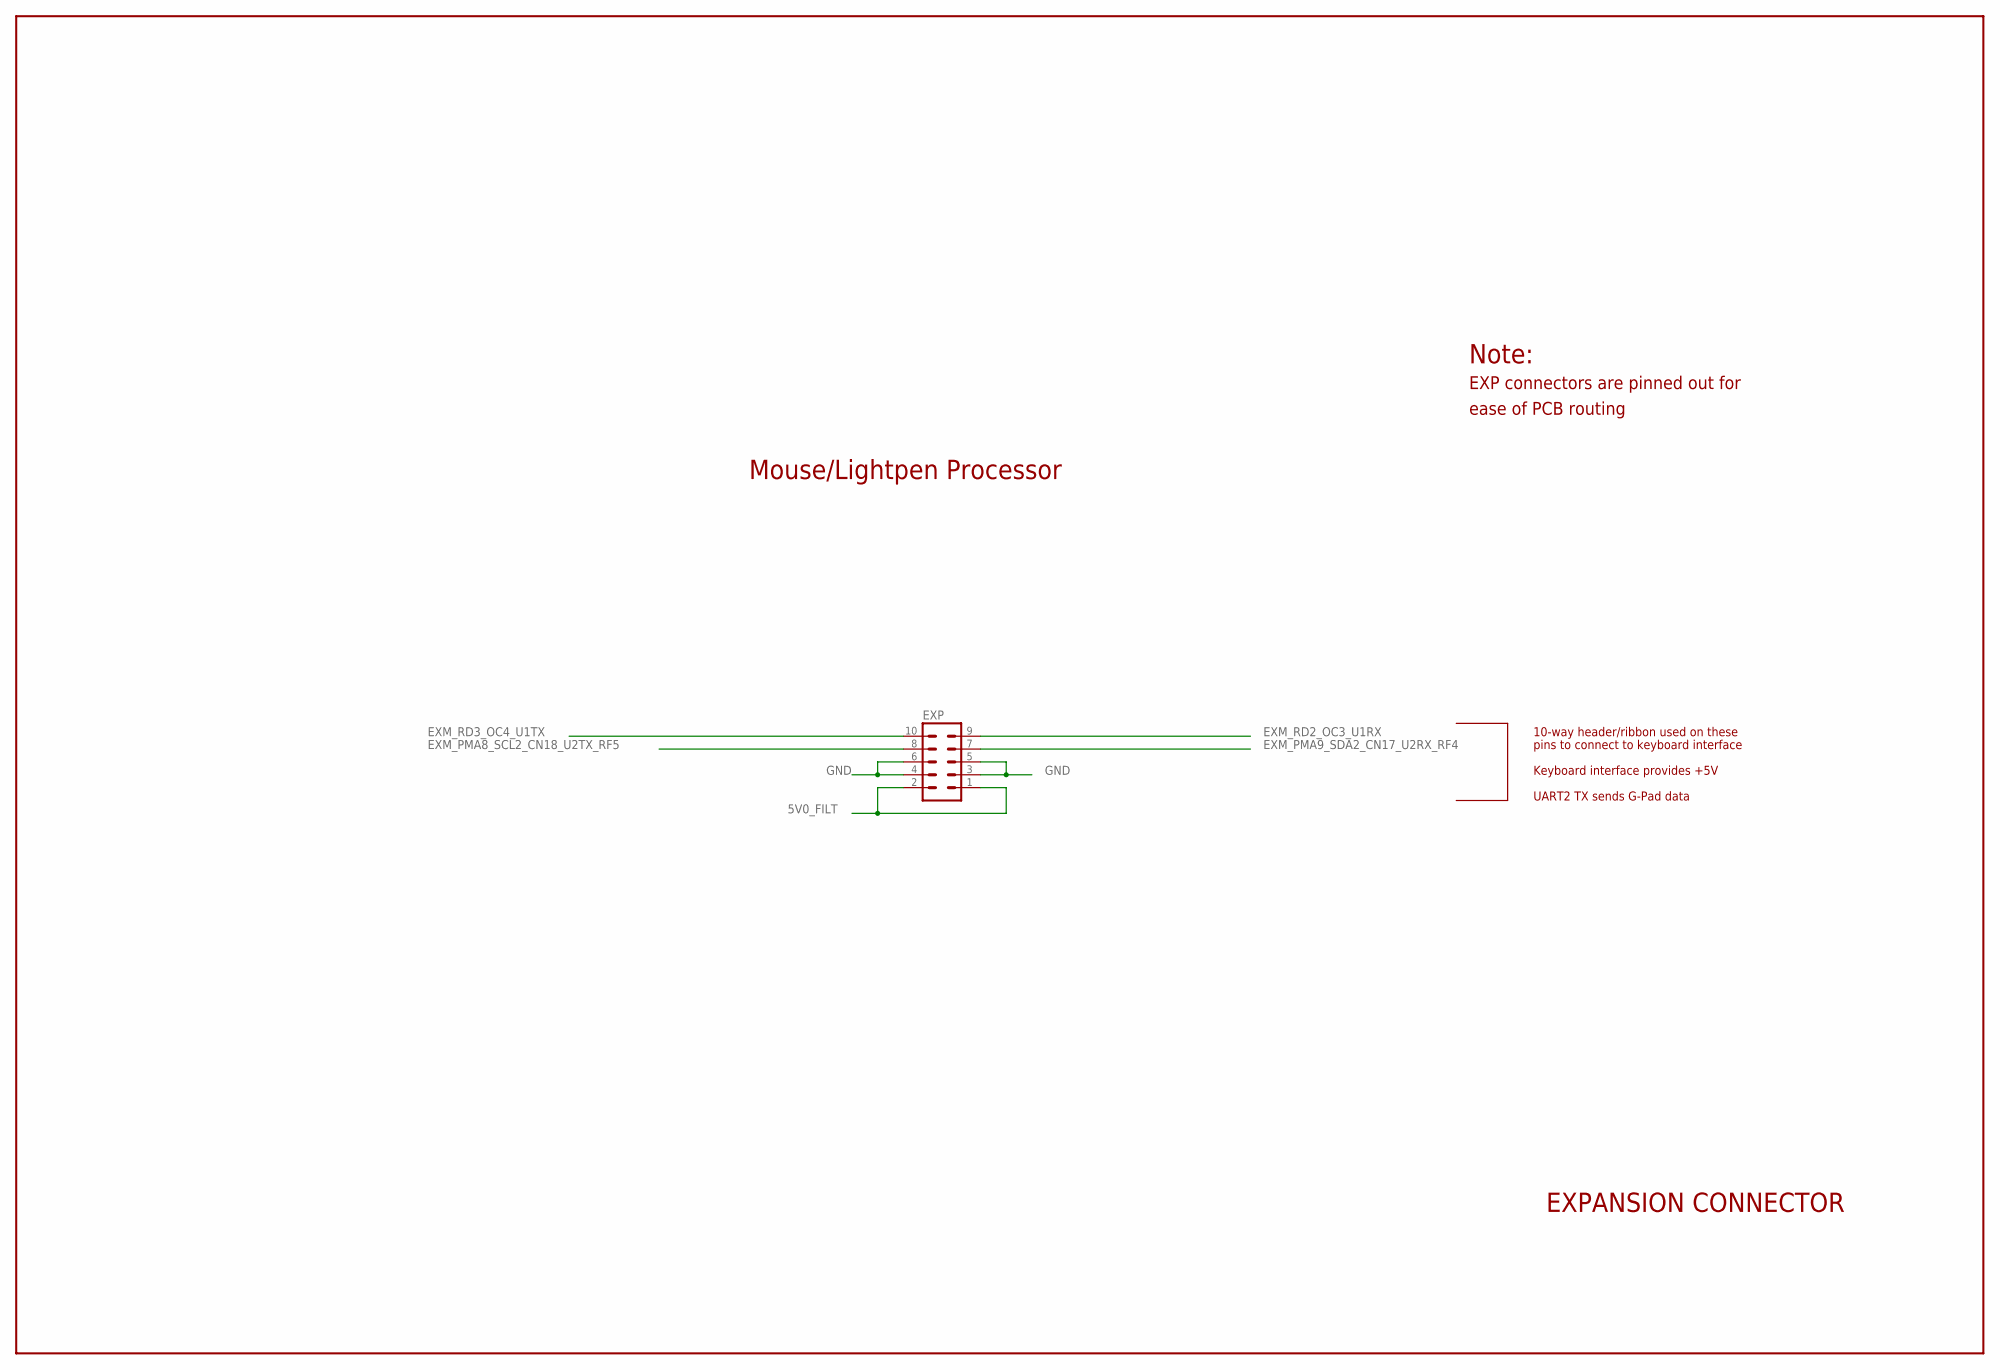
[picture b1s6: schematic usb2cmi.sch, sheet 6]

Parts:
EXP: MA05-2

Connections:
5V0_FILT: EXP.1, EXP.2; also elsewhere on the board
EXM_PMA8_SCL2_CN18_U2TX_RF5: EXP.8; also elsewhere on the board
EXM_PMA9_SDA2_CN17_U2RX_RF4: EXP.7; also elsewhere on the board
EXM_RD2_OC3_U1RX: EXP.9; also elsewhere on the board
EXM_RD3_OC4_U1TX: EXP.10; also elsewhere on the board
GND: EXP.3, EXP.4, EXP.5, EXP.6; also elsewhere on the board

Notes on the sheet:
Mouse/Lightpen Processor
EXPANSION CONNECTOR
Note:
EXP connectors are pinned out for
ease of PCB routing
10-way header/ribbon used on these
pins to connect to keyboard interface
Keyboard interface provides +5V
UART2 TX sends G-Pad data

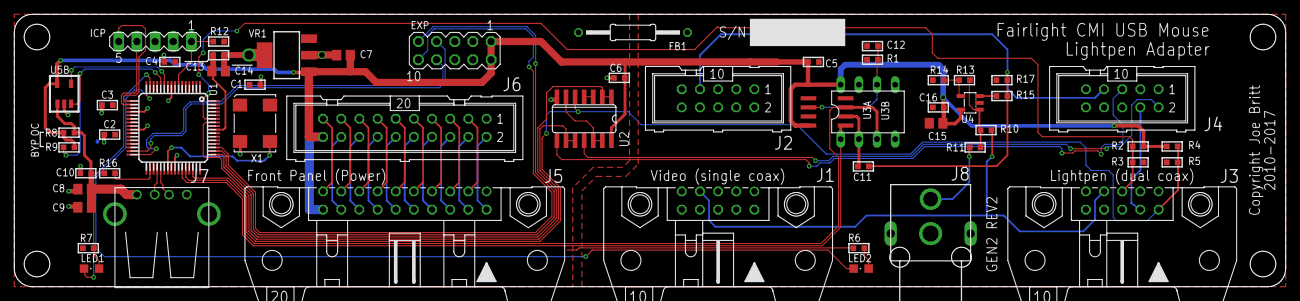
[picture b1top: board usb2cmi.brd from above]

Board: 2 copper layers, 177.8 x 38.1 mm, 54 parts (0 on the bottom side), 60 nets.

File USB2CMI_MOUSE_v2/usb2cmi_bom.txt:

total boards:	20						
								
shortfall	on hand	total	per board					
		Qty	Qty	Value	Device	Parts	supplier	NOTES
11	9	20	1		L-US0207/15	FB1	HSC	
0	20	20	1		MA20-2 *NOTE*	EXP	personal surplus	"mount 2x 5 pin header at pin 1, cut down longer ones"
116	84	200	10	.1uF	C_0603	"C1, C2, C3, C4, C5, C6, C9, C10, C11, C21"	HSC	
0	28	20	1	0	R_0603	R16	HSC	
11	9	20	1	1N4002	1N4002	D1	HSC	
16	4	20	1	8 MHz	CTS-OSC	X1	Mouser	
0	29	20	1	10K	R_0603	R12	HSC	
0	80	40	2	33uF	CPOL-US085CS-1AR	"C7, C22"	personal surplus	
0	29	20	1	51	R_0603	R7	HSC	
0	29	20	1	56	R_0603	R6	HSC	
16	4	20	1	74LS00D	74LS00D	U2	"HSC, Mouser"	
20	0	20	1	100uF	CPOL-USCT6032	C8	Mouser	
0	57	40	2	220	R_0603	"R3, R5"	HSC	
0	57	40	2	330	R_0603	"R2, R4"	HSC	
20	0	20	1	680K	R_0603	R1	HSC	
0	59	20	1	DANGER_POWER	DANGER_POWER	J4	personal surplus	
0	34	20	1	HSC_STACKED	HSC_STACKED	LED1	HSC	
								
20	0	20	1	LM1881SO	LM1881SO	U3B	"Jameco, Digikey, Mouser"	
6	14	20	1	LT1963A-3.3	LINEAR-REG-SOT223	VR1	Digikey	LT1963AEST-3.3#PBF-ND
11	9	20	1	NC5FAH	NC5FAH	J2		
11	9	20	1	NC5MBH	NC5MBH	J1		
12	8	20	1	PIC32MX440FH	PIC32MX440FH	U1		
0	24	20	1	RCA-HSC	RCA-HSC	J3		
0	34	20	1	RJ11	RJ11	ICP		
								
20	0	20	1	TPS2051BDBV	TPS2041BDBV	U5B	Mouser	
20	0	20	1	USB-A-H	USB-A-H	J5

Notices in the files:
mouse/cmi_mouse-framework.c:
Lightpen emulation code Copyright 2010 Joe Britt (britt@shapetable.com).
All rights reserved.  Released under the 2-clause BSD license:
Redistribution and use in source and binary forms, with or without modification, are
USB2CMI_MOUSE_v2/Series_I_power.brd:
Copyright Joe Britt 2017
